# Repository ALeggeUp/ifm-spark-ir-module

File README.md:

# IFM Spark IR Module

IR module for IFM Spark Dev

# License

This work is licensed under the Creative Commons Attribution 4.0 International License. To view a copy of this license, visit http://creativecommons.org/licenses/by/4.0/ or send a
letter to Creative Commons, PO Box 1866, Mountain View, CA 94042, USA.

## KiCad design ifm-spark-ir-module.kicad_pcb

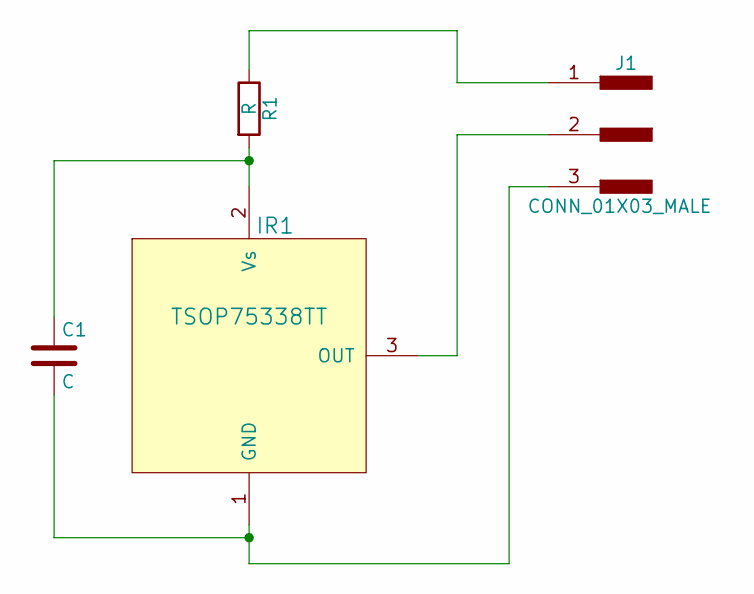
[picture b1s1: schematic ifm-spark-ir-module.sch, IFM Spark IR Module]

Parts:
C1: C; C_0805_HandSoldering
IR1: TSOP75338TT; TSOP75x; MPN TSOP75338TT
J1: CONN_01X03_MALE; Pin_Header_Straight_1x03_Pitch2.54mm
R1: R; R_0805_HandSoldering

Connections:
GND: C1.2, IR1.1 (GND), IR1.4 (GND), J1.3
unnamed: C1.1, IR1.2 (Vs), R1.2
unnamed: IR1.3 (OUT), J1.2
unnamed: J1.1, R1.1

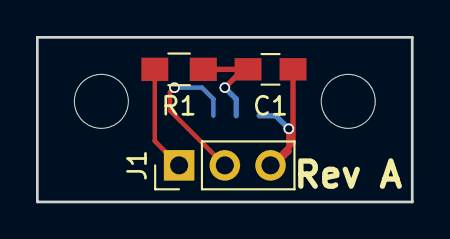
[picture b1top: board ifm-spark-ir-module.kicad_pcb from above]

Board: 2 copper layers, 20.8 x 9.1 mm, 4 parts (1 on the bottom side), 4 nets.

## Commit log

2017-05-26 Add License information
2017-05-26 New KiCad project for IFM Spark IR Module
2017-05-26 Created symbol for TSOP75338TT and added to schematic
2017-05-26 Library referenced for TSOP75338TT
2017-05-26 Add TSOP75x footprint/module
2017-05-26 Added in passives and connector and wired it up
2017-05-26 Brought footprints into board and set up design rules
2017-05-27 Filled ground-plane
